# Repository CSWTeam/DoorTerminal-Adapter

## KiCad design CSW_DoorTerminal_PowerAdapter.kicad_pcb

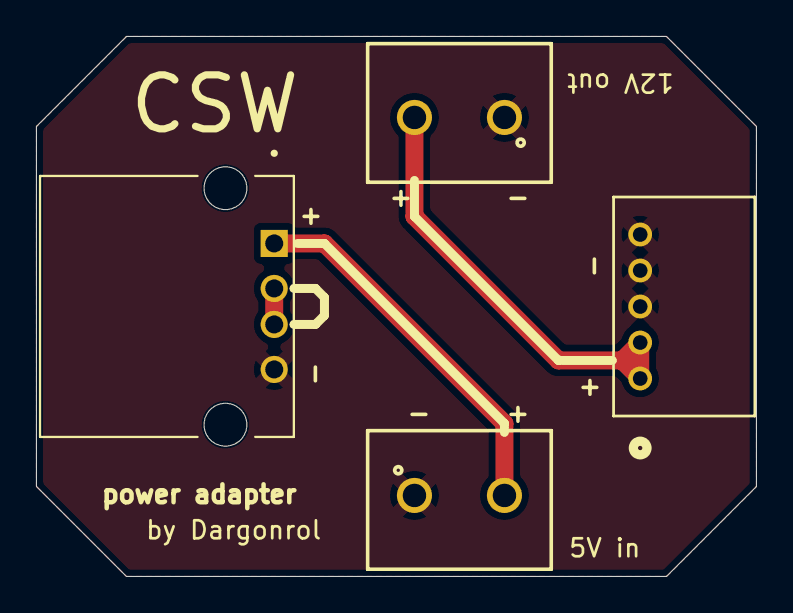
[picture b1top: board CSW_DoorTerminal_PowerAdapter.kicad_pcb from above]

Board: 2 copper layers, 40.0 x 30.0 mm, 4 parts (0 on the bottom side), 4 nets.

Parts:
J1: USB_A; OST_USB-A1HSW6
J2: S5B-PH-K-S; CONN_S5B-PH-K-S_JST
J3, J4: Screw_Terminal_01x02; 691137710002

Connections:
/GND: J1.4 (GND), J2.3, J2.4, J2.5, J3.1, J4.1
/Vcc: J1.1 (VBUS), J3.2
/Vee: J2.1, J2.2, J4.2
unnamed: J1.2 (D-), J1.3 (D+)

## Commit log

2026-05-22 finished pcb
2026-05-23 added some metadata
